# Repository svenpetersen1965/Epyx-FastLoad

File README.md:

# Epyx-FastLoad
A rebuild of the Epyx Fast Load cartridge for the Commodore C64 in the same format like the <a href="https://github.com/bwack/Versa64Cart">Versa64Cart<a>,
The dimensions are the same and the location of the reset switch is the same.

The software and the user manual can be obtained from this website: <a href="https://rr.pokefinder.org/wiki/Epyx_FastLoad">Epyx FastLoad (pokefinder)</a>  

# BOM value
The bom value is 8€, which includes the M27C512 EPROM. It was calculated with domestic prices. 

# Rev. 1
There is a jumper for selecting the software versions (there is obviously more than one version).
  
# Rev. 2
Rev. 2 is only a mechanical revision. Notches for tfw8bit.com Stumpy cartridge case were added. 

There is a version of the Gerber files and the eagle file without a documentation frame, since some PCB manufacturer's websites have a problem with it.

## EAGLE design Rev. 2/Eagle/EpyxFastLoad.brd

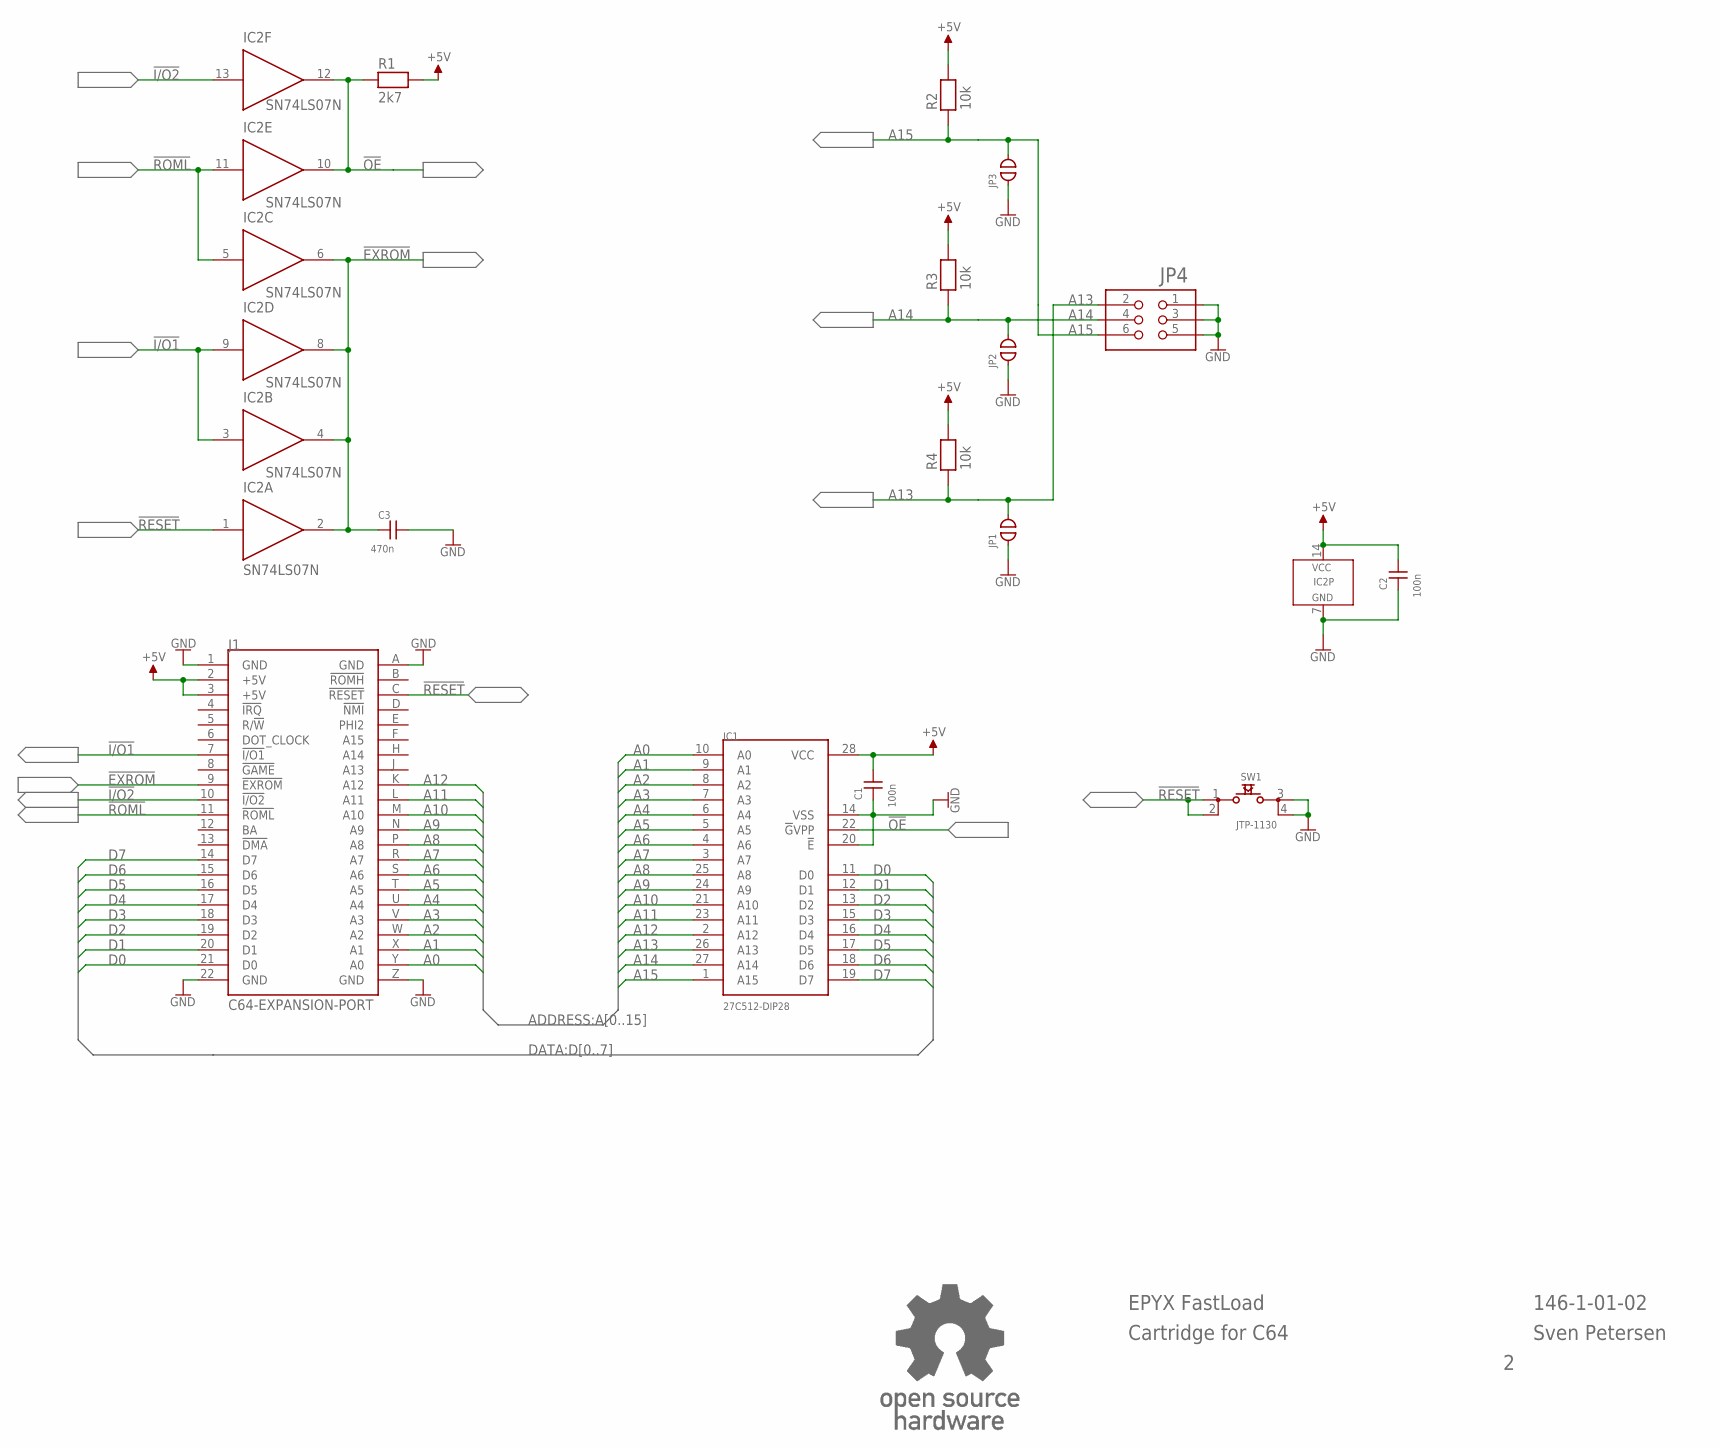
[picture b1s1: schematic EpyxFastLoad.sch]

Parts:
C1, C2: 100n; C-2,5
C3: 470n; C-5
IC1: 27C512-DIP28; DIL28-6
IC2: SN74LS07N; DIL-14
J1: C64-EXPANSION-PORT; EXPANSIO_SQ
JP1, JP2, JP3: OPEN; CP_OP
JP4: PINHD-2X390°; 2X03_90_SERIES_088
R1: 2k7; R-10
R2, R3, R4: 10k; R-10
SW1: JTP-1130
U$39: OPEN_SOURCE_HW; OPENHW

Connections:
!EXROM: C3.1, IC2.2 (O), IC2.4 (O), IC2.6 (O), IC2.8 (O), J1.9 (!EXROM)
!I/O1: IC2.3 (I), IC2.9 (I), J1.7 (!I/O1)
!I/O2: IC2.13 (I), J1.10 (!I/O2)
!OE: IC1.22 (!G!VPP), IC2.10 (O), IC2.12 (O), R1.1
!RESET: IC2.1 (I), J1.C (!RESET), SW1.1, SW1.2
!ROML: IC2.5 (I), IC2.11 (I), J1.11 (!ROML)
+5V: C1.2, C2.2, IC1.28 (VCC), IC2.14 (VCC), J1.2 (+5V), J1.3 (+5V), R1.2, R2.2, R3.2, R4.2
A0: IC1.10 (A0), J1.Y (A0)
A1: IC1.9 (A1), J1.X (A1)
A2: IC1.8 (A2), J1.W (A2)
A3: IC1.7 (A3), J1.V (A3)
A4: IC1.6 (A4), J1.U (A4)
A5: IC1.5 (A5), J1.T (A5)
A6: IC1.4 (A6), J1.S (A6)
A7: IC1.3 (A7), J1.R (A7)
A8: IC1.25 (A8), J1.P (A8)
A9: IC1.24 (A9), J1.N (A9)
A10: IC1.21 (A10), J1.M (A10)
A11: IC1.23 (A11), J1.L (A11)
A12: IC1.2 (A12), J1.K (A12)
A13: IC1.26 (A13), JP1.2, JP4.2, R4.1
A14: IC1.27 (A14), JP2.2, JP4.4, R3.1
A15: IC1.1 (A15), JP3.2, JP4.6, R2.1
D0: IC1.11 (D0), J1.21 (D0)
D1: IC1.12 (D1), J1.20 (D1)
D2: IC1.13 (D2), J1.19 (D2)
D3: IC1.15 (D3), J1.18 (D3)
D4: IC1.16 (D4), J1.17 (D4)
D5: IC1.17 (D5), J1.16 (D5)
D6: IC1.18 (D6), J1.15 (D6)
D7: IC1.19 (D7), J1.14 (D7)
GND: C1.1, C2.1, C3.2, IC1.14 (VSS), IC1.20 (!E), IC2.7 (GND), J1.1 (GND), J1.22 (GND), J1.A (GND), J1.Z (GND), JP1.1, JP2.1, JP3.1, JP4.1, JP4.3, JP4.5, SW1.3, SW1.4

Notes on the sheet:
EPYX FastLoad
Sven Petersen
146-1-01-02
Cartridge for C64

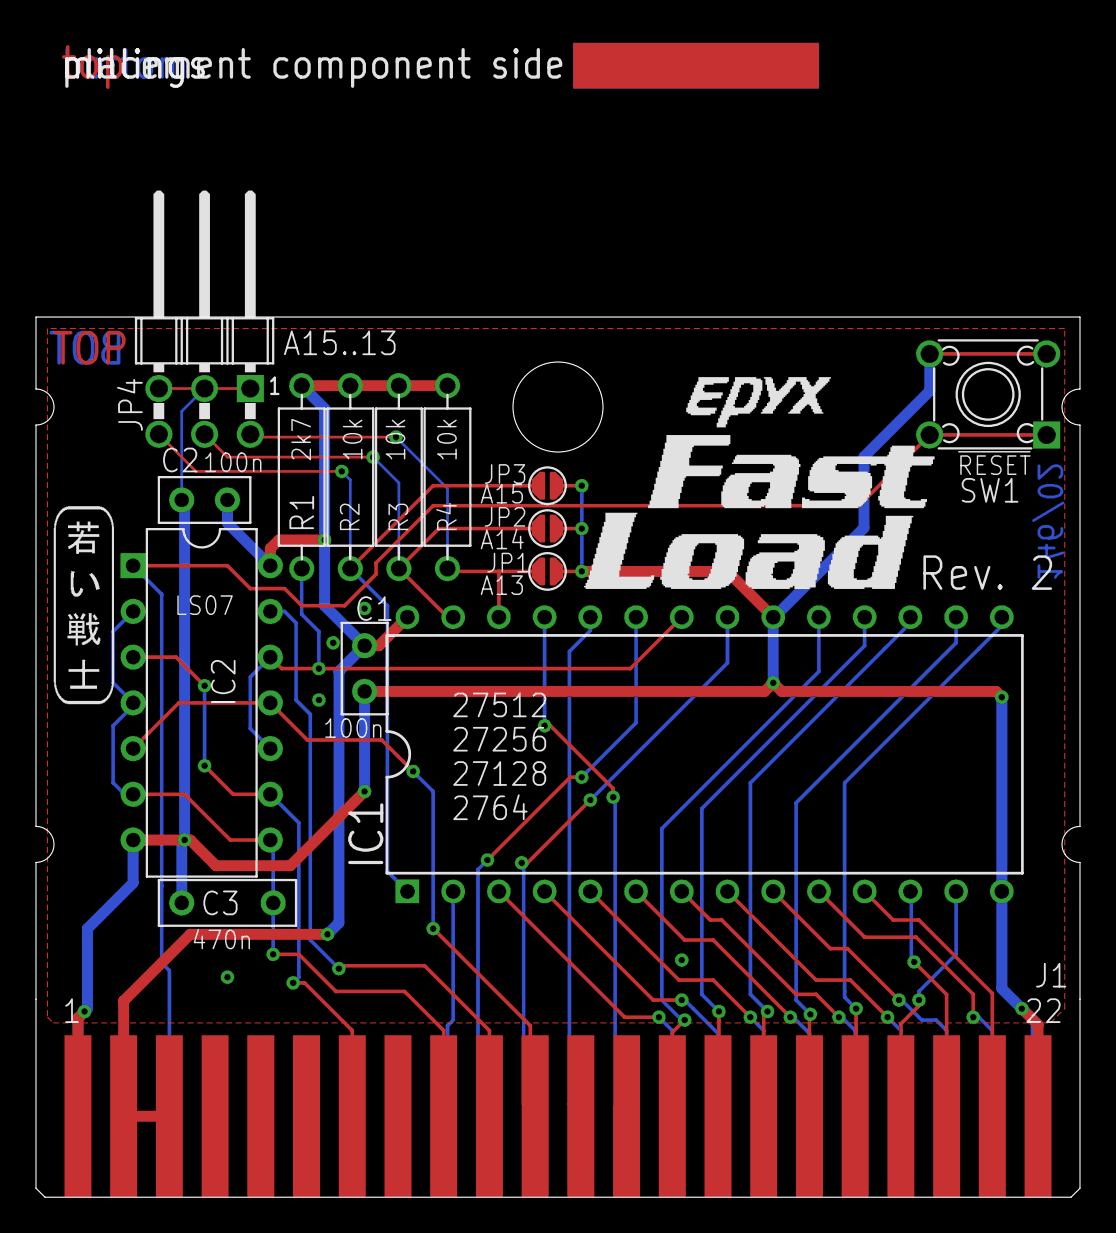
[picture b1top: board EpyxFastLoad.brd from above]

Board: 2 copper layers, 58.0 x 64.5 mm, 20 parts (1 on the bottom side), 32 nets.

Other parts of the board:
U$11: EPYXFL
U$40: 2LAYER
U$41: PCB-TITLE/
U$42: SVEN_TAG

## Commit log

2020-08-08 Silk Screen Update
2020-08-08 Rev. 1 released
2021-06-03 Cartridge Label as PNG
2022-10-24 Rev. 2 uploaded
